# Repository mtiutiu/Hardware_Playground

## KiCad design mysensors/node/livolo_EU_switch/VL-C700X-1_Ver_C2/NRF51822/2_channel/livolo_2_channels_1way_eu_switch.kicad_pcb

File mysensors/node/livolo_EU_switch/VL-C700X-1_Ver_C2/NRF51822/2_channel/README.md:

## Mysensors NRF51822 Livolo 2 channels 1 way EU switch front module

##### 3D renderings of pcb

Top view | Bottom view
------------ | -------------
 | 

**Description:**

This is a Mysensors replica of the Livolo EU Switch(2 channels 1 way) front plate for the **VL-C702X-2_Ver_C1** Livolo hw revision.

**Key Features:**

 - **Capacitive touch sensing** using **MTCH105** specialized IC
 - **MySensors** ready(NRF51822)
 - **DC-DC Buck converter** for powering from the 12V line ( the DC-DC converter can be bypassed and not used at all if desired by soldering the **3V_EN** jumper and removing the L1 ferrite bead or by not soldering the dc-dc converter components)

**Firmware programming and testing steps for MySensors:**
1. Install Arduino IDE
2. Install nrf5 arduino core from here: https://github.com/sandeepmistry/arduino-nRF5
3. Select the **nrf51 generic board (16K ram and 256K flash)** variant(or nrf52 generic if you have a nrf52832 device)
4. The low frequency oscillator needs to be set to **RC oscillator** in the Arduino menu
5. **NO Softdevice** needs to be selected
6. Use a st-link v2 programmer
7. You need to connect only: SWD, SWCLK, Vdd and GND
8. Load your MySensors sketch or use the one provided with this project 

**Firmware programming and testing steps for BLE:**
1. Install Arduino IDE
2. Install nrf5 arduino core from here: https://github.com/sandeepmistry/arduino-nRF5
3. install Arduino ble peripheral library from here: https://github.com/sandeepmistry/arduino-BLEPeripheral
4. Install the required softdevice as explained here: https://github.com/sandeepmistry/arduino-nRF5#selecting-a-softdevice
5. Select the **nrf51 generic board (16K ram and 256K flash)** variant(or nrf52 generic if you have a nrf52832 device)
6. The low frequency oscillator needs to be set to **RC oscillator** in the Arduino menu
7. Select **S130** softdevice from menu if you have nrf51(or S132 if you have nrf52)
8. Use a st-link v2 programmer
9. You need to connect only: SWD, SWCLK, Vdd and GND
10. Load my BLE testing sketch, compile and upload
11. Use the nrf connect tool for Android: https://play.google.com/store/apps/details?id=no.nordicsemi.android.mcp&hl=en
12. Scan for available devices - you should see a "Livolo Lights" device
13. Connect to it
14. After connecting and characteristics discovery -> expand one of the "unknown characteristic"(there's one for each livolo channel or relay)
15. Use the button with an UP arrow on it to send values - select **UINT8** - send 1 for turning ON the light, send 0 for turning OFF the light for the selected channel

**Extra steps needed for the Livolo power supply/relays board!!!**
 1. The R3 resistor(marked with 104 - 100Kohm) near the bridge rectifier needs to be replaced with a 1Kohm one(1206 package)
 2. The R13 SMD resistor needs to be replaced with a solder bridge
 3. Mount a X2 capacitor of 1uF - 2.2uF rated at a minimum of 275Vac directly on the light bulb(in parallel)

**Notes:**
 - If using BLE based firmware with this board the current consumption on average is only **5mA **for the **WHOLE BOARD**(including leds) and this is **constant** over time
 - If using MySensors firmware instead the current consumption on average increases to **18-20mA **which is 4 times bigger than BLE
 - What I noticed is that the original Livolo power supply(the one used in stand-by mode) is designed to work with currents of 1mA or even below so that's why the above hardware modifications(the extra steps) need to be performed - otherwise the switch won't start
 - It's not advised to replace the R3 resistor with a bridge only as the stand-by power supply may be damaged over time and it's required that the custom top board(for which the current project was made for) to draw a lower current as much as possible(ideally would be several milliamps and even lower but it works with 10-20mA also)

**Practical usage ideas:**
 - Currently(and based on my previous experience with this kind of project) I will use all the Livolo switches preloaded with BLE firmware because of the lower current consumption AND in each room there will be a BLE Central node(based on Raspberry PI Zero W) - see this project: [RFM69W Raspberry PI Zero(W) Shield(HAT)](https://www.openhardware.io/view/487/RFM69W-Raspberry-PI-ZeroW-ShieldHAT) which will route messages to/from the Livolo switches BLE Peripherals to the MySensors network.

**HW Revisions:**
 - 0.1 - initial hw design
 - 0.2 - switched to MTCH105 touch sensor
 - 0.3 - added 3V line jumper

If this project was of any help you can buy me a beer or at least support my effort by using the below button. Thanks.

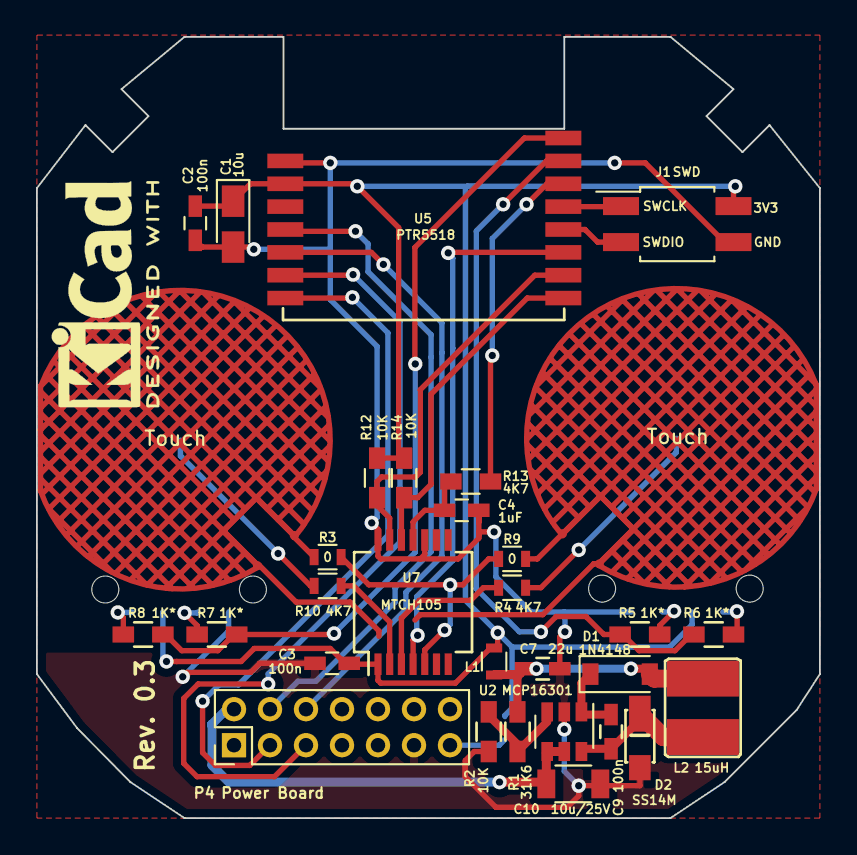
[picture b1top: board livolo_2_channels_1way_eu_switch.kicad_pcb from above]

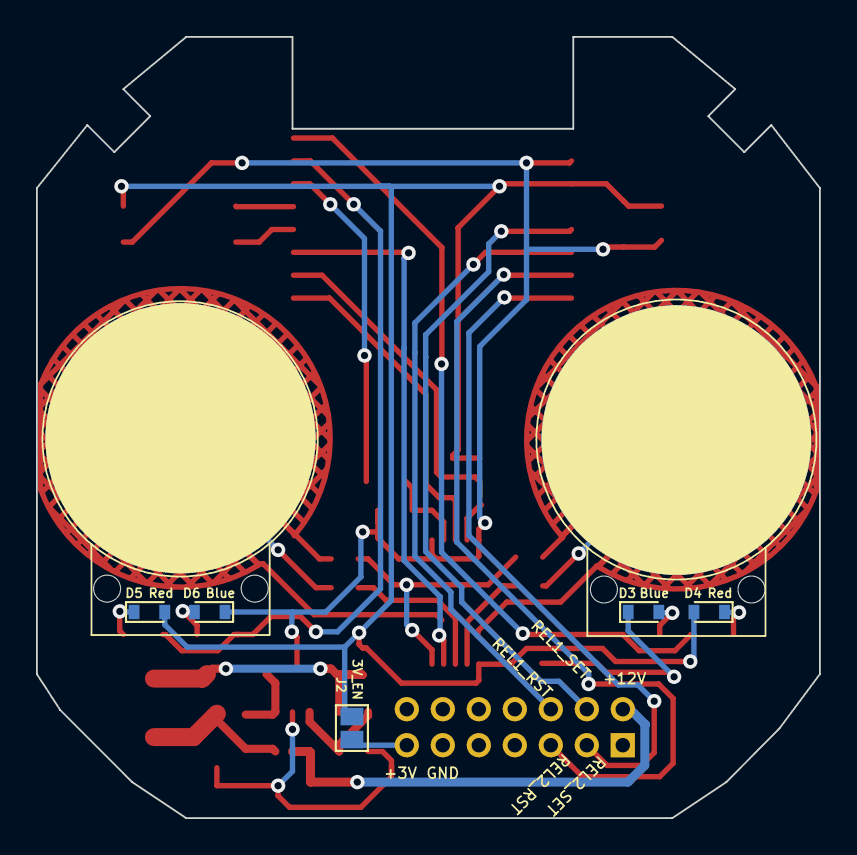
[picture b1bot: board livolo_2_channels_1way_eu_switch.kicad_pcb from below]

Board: 2 copper layers, 43.5 x 43.4 mm, 36 parts (5 on the bottom side), 32 nets.

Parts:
C1: 10u; CP_Tantalum_Case-R_EIA-2012-12_Wave
C2, C3, C9: 100n; C_0603_HandSoldering
C4: 1uF; C_0603_HandSoldering
C7: 22u; C_0603_HandSoldering
C10: 10u/25V; C_1206
D1: 1N4148; SOD-123
D2: SS14M
D3, D6: Blue; D_0603
D4, D5: Red; D_0603
J1: SWD; Pin_Header_Straight_2x02_Pitch2.00mm_SMD
J2: 3V_EN; GS2
L1: BLM18HE152SN1D; R_0603
L2: 15uH; VLCF4020T-150MR68
P4: Power Board; Pin_Header_Straight_2x07_Pitch2.00mm
R1: 31K6; R_0603_HandSoldering
R2, R12, R14: 10K; R_0603_HandSoldering
R3, R9: 0; R_0603
R4, R10: 4K7; R_0603
R5, R6, R7, R8: 1K*; R_0603_HandSoldering
R13: 4K7; R_0603_HandSoldering
U1: Touch; livolo_ts_guard_cut_left
U2: MCP16301; SOT-23-6
U5: PTR5518
U6: Touch; livolo_ts_guard_cut_right
U7: MTCH105; SSOP-14_5.3x6.2mm_Pitch0.65mm

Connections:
+3V3: C1.1, C2.2, C3.1, D4.2, D5.2, J1.2, J2.2, L1.2, R12.1, R14.1, U5.10, U7.1
/12Vcc: C10.1, P4.2, U2.4, U2.5
/MTPM: U5.3, U7.4
/MTSA: R13.1, U5.6
/Relay1_Reset: P4.6, U5.13
/Relay1_Set: P4.4, U5.12
/Relay2_Reset: P4.3, U5.15
/Relay2_Set: P4.5, U5.14
/S1_LEDs: R5.2, R6.2, U5.7
/S2_LEDs: R7.2, R8.2, U5.8
/SWCLK: J1.1, U5.5
/SWDIO: J1.3, U5.4
/TS1: R12.2, U5.2, U7.13
/TS2: R14.2, U5.1, U7.12
GND: C1.2, C2.1, C3.2, C4.1, C7.2, C10.2, D2.2, D3.1, D6.1, J1.4, P4.11, R2.1, U2.2, U5.9, U7.10, U7.14
unnamed: C4.2, R13.2, U7.11
unnamed: C7.1, D1.2, L1.1, L2.1, R1.2
unnamed: C9.1, D1.1, U2.1
unnamed: C9.2, D2.1, L2.2, U2.6
unnamed: D3.2, R7.1
unnamed: D4.1, R8.1
unnamed: D5.1, R6.1
unnamed: D6.2, R5.1
unnamed: J2.1, P4.13
unnamed: R1.1, R2.2, U2.3
unnamed: R3.1, U1.2
unnamed: R3.2, R9.1, U7.5
unnamed: R4.1, U7.3
unnamed: R4.2, U6.1
unnamed: R9.2, U6.2
unnamed: R10.1, U1.1
unnamed: R10.2, U7.2

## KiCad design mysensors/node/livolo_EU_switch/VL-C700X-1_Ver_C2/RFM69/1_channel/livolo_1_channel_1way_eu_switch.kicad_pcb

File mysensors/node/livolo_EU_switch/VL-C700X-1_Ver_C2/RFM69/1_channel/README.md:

## Mysensors RFM69 Livolo 1 channel 1 way EU switch front module

##### 3D renderings of pcb

Top view | Bottom view
------------ | -------------
 | 

**Description:**

This is a Mysensors replica of the Livolo EU Switch(1 channel 1 way) front plate for the **VL-C702X-2_Ver_C1** Livolo hw revision.

**Key Features:**

 - **Capacitive touch sensing** using **TTP223** specialized IC
 - **AT25DF512C-SSHN-B** SPI flash module for OTA
 - **ATSHA204A** for signing
 - **MySensors** ready(Atmega328p + RFM69CW)
 - **DC-DC Buck converter** in combination with a **linear LDO voltage regulator** for efficient **noise cancelling**
  (the used LDO reduces a little bit the Buck's converter current capability - down to 150mA from 600mA but this is not important as the whole board takes about 60mA at peak)

**Work progress:**
 1. Test/verify the pcb board correctness(from both electrical and mechanical point of views) - **IN PROGRESS**
 2. Produce the initial PCB's using some external PCB manufacturer
 3. Components assembly(soldering)
 4. Create Mysensors sketch code
 5. Verify the real board with running code
 6. Verify OTA

**HW Revisions:**
 - 0.1 - initial hw design

The only thing I ask if using this project is to at least mention my name and if I don't ask too much you can also support my effort using the below button. Thanks.

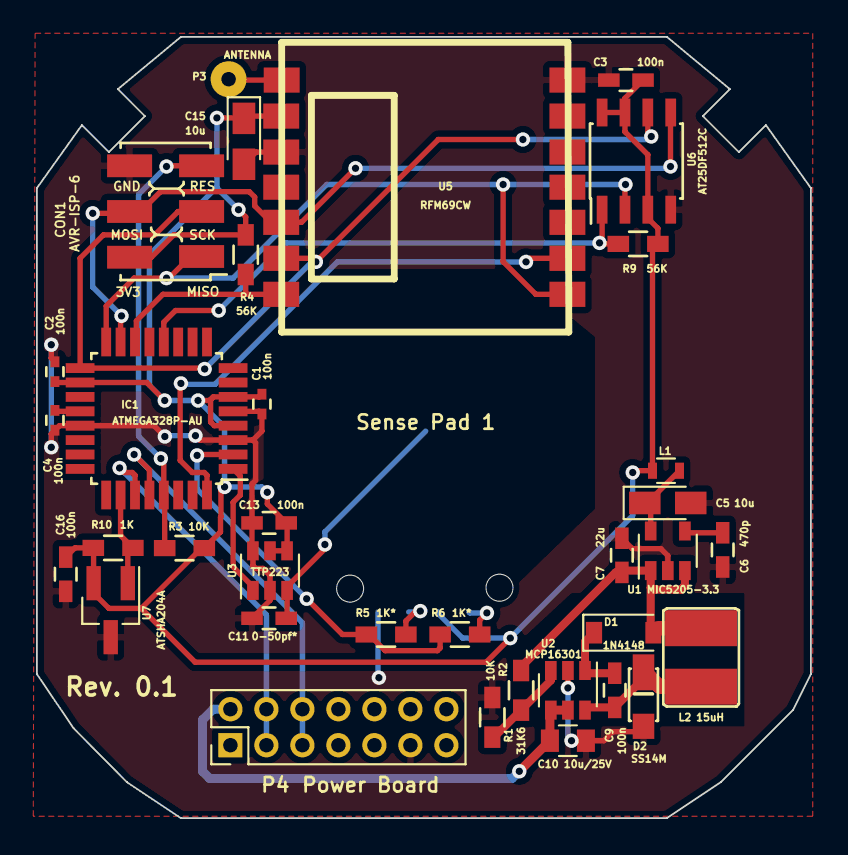
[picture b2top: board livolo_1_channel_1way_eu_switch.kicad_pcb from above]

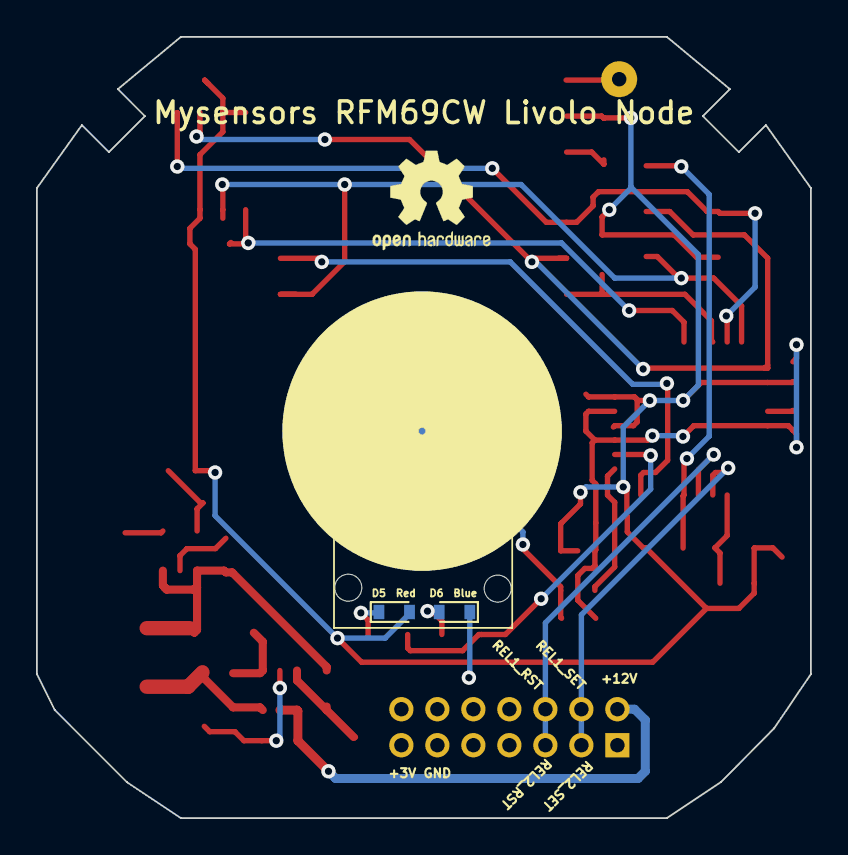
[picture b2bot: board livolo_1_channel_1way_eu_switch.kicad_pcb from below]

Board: 2 copper layers, 43.0 x 43.4 mm, 38 parts (2 on the bottom side), 26 nets.

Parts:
C1, C2, C4: 100n; C_0402
C3, C9, C13, C16: 100n; C_0603_HandSoldering
C5, C15: 10u; CP_Tantalum_Case-R_EIA-2012-12_Wave
C6: 470p; C_0603_HandSoldering
C7: 22u; C_0603_HandSoldering
C10: 10u/25V; C_0805
C11: 0-50pf*; C_0603_HandSoldering
CON1: AVR-ISP-6; AVR_ISP_SMT_Small_02x03
D1: 1N4148; SOD-123
D2: SS14M
D5: Red; D_0603
D6: Blue; D_0603
IC1: ATMEGA328P-AU; TQFP-32_7x7mm_Pitch0.8mm
L1: BLM18HE152SN1D; R_0603
L2: 15uH; VLCF4020T-150MR68
P1: Sense Pad 1; touch_pad_16mm
P3: ANTENNA; SolderWirePad_single_0-8mmDrill
P4: Power Board; Pin_Header_Straight_2x07_Pitch2.00mm
R1: 31K6; R_0603_HandSoldering
R2, R3: 10K; R_0603_HandSoldering
R4, R9: 56K; R_0603_HandSoldering
R5, R6: 1K*; R_0603_HandSoldering
R10: 1K; R_0603_HandSoldering
U1: MIC5205-3.3; SOT-23-5
U2: MCP16301; SOT-23-6
U3: TTP223; SOT-23-6
U5: RFM69CW
U6: AT25DF512C; SOIC-8_3.9x4.9mm_Pitch1.27mm
U7: ATSHA204A; SOT-23_Handsoldering

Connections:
+3V3: C1.1, C2.2, C3.2, C13.1, C15.1, C16.2, CON1.2, D5.2, IC1.4, IC1.6, IC1.18, L1.1, R3.1, R4.2, R9.1, R10.1, U3.4, U3.5, U5.2, U6.3, U6.7, U6.8, U7.2
/12Vcc: C10.1, P4.2, U2.4, U2.5
/ATSHA204A: IC1.26, R10.2, U7.1
/FLASH_SS: IC1.12, R9.2, U6.1
/INT: IC1.32, U5.9
/MISO: CON1.1, IC1.16, U5.8, U6.2
/MOSI: CON1.4, IC1.15, U5.5, U6.5
/RADIO_SS: IC1.14, R4.1, U5.7
/RESET: CON1.5, IC1.29, R3.2
/Relay1_Reset: IC1.28, P4.5, P4.6
/Relay1_Set: IC1.27, P4.3, P4.4
/S1_LEDs: IC1.2, R5.2, R6.2
/SCK: CON1.3, IC1.17, U5.6, U6.6
/TS1: IC1.1, U3.1
GND: C1.2, C2.1, C3.1, C4.1, C5.2, C6.2, C7.2, C10.2, C11.2, C13.2, C15.2, C16.1, CON1.6, D2.2, D6.1, IC1.3, IC1.5, IC1.21, P4.11, R2.1, U1.2, U2.2, U3.2, U3.6, U5.3, U5.14, U6.4, U7.3
unnamed: C4.2, IC1.20
unnamed: C5.1, L1.2, U1.5
unnamed: C6.1, U1.4
unnamed: C7.1, D1.2, L2.1, R1.2, U1.1, U1.3
unnamed: C9.1, D1.1, U2.1
unnamed: C9.2, D2.1, L2.2, U2.6
unnamed: C11.1, P1.1, U3.3
unnamed: D5.1, R6.1
unnamed: D6.2, R5.1
unnamed: P3.1, U5.1
unnamed: R1.1, R2.2, U2.3
